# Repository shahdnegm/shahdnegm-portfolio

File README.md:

# Shahd Negm | Manufacturing Systems & Engineering Portfolio

**Mechatronics Engineering graduate · MSc Engineering Management student**  
**Focus:** Manufacturing Execution Systems (MES) · Manufacturing Operations Management (MOM) · Smart Manufacturing · Quality & Production Data

I bring hands-on manufacturing experience using **MES at Schaeffler**, alongside academic work in automated inspection, reliability simulation and manufacturing process improvement.

## Shop-floor MES experience

At **Schaeffler**, I used the manufacturing execution system to:
- Track production items and inspect their manufacturing history and **traceability**.
- Check and record quality-related information and **quality decisions**, including whether an item was marked for **scrap or rework**.
- Verify the **next step** in an item's production workflow.
- Record completed process steps so the item's manufacturing progress could be followed.

This describes **operational use of an existing MES**, not software development or system administration. My experience supports my interest in improving the digital connection between quality decisions and shop-floor execution.

## Featured manufacturing projects

| Project | Problem / technical contribution | Evidence |
|---|---|---|
| [AI-Powered Automated Optical Inspection](projects/automated-optical-inspection/README.md) | Built a vision-based inspection prototype integrating quality decisions and traceability logging | [Peer-reviewed first-author publication](https://doi.org/10.1007/s00170-026-18704-3); 33-bottle benchmark |
| [Monte Carlo Production-Line Reliability](projects/monte-carlo-reliability.md) | Analysed buffer sizing, failures, preventive maintenance, throughput and bottlenecks | Team evaluated 125 configurations, 1,000 replications each |
| [Unilever Industrial Engineering Competition](projects/unilever-industrial-engineering.md) | Designed manufacturing-flow and changeover improvement concepts | Quantified *proposed* time reductions and estimated business impact |
| [Olist E-Commerce Delivery Reliability — Six Sigma DMAIC](projects/olist-delivery-dmaic/README.md) | Historical order-level delivery KPI analysis, freight/geography segmentation, Ishikawa and proposed pilot/control plans | 96,470 eligible deliveries; 6.77% provisional date-based late rate |
| [Fapofa Quality & Process Improvement](projects/fapofa-process-improvement.md) | Mapped processes and proposed quality-control and Lean improvements | Team academic case study using Pareto, Fishbone and PDCA |

## Other technical projects

- [Robotic Manipulator Arm](projects/robotic-manipulator-arm/README.md) — design and control reports, 11 mechanical drawings, KiCad electronics, MATLAB code and Simulink model.
- [Line-Following Robot](projects/line-follower-robot.md) — sensors, Arduino and drive control.

## Technical toolkit

**Manufacturing & quality:** MES workflow use, item traceability, scrap/rework decisions, AOI/X-ray inspection, process mapping, SMED, PDCA.  
**Analysis & simulation:** Python, Excel, Monte Carlo simulation, reliability analysis, production KPIs, MATLAB/Simulink.  
**Automation & inspection:** YOLOv8, image processing, OCR, PLC interface concepts and CAD.

## Publication

Negm, Shahd Ayman, et al. (2026). *Vision-based automated optical inspection for real-time quality control: hybrid single-camera deep-learning AOI for mixed-SKU bottling lines.* *The International Journal of Advanced Manufacturing Technology*. [Read publication](https://doi.org/10.1007/s00170-026-18704-3).

## Attribution and sharing policy

Monte Carlo and Fapofa were **academic team projects**. Pages distinguish individual and team contributions. Simulated results, proposed targets and estimated savings are **not implemented industrial outcomes**. The Monte Carlo workbook and Python simulation are public; the AOI project's scripts and datasets are not publicly released.

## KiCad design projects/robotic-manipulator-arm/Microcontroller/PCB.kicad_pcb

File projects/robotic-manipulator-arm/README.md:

# Four-DOF Robotic Manipulator Arm

Academic mechatronics project · University of Debrecen · 2025

A four-degree-of-freedom robotic-arm design for light industrial drilling, combining mechanical design, motor and encoder selection, a KiCad controller design, and MATLAB/Simulink motor-control modelling.

## Project figures

*Final CAD assembly — design report Fig. 2, PDF p. 4.*

*KiCad motor-controller PCB — design report Fig. 3, PDF p. 6.*

*Simulated controller-response comparison — design report Fig. 6, PDF p. 8.*

[Browse all seven original figures](GALLERY.md), including the base CAD, wiring diagram, cascade-current response and Simulink control structure.

## Project files

| Area | Files |
|---|---|
| Design report | [Project description](Project-description.pdf) |
| Motor-control report | [PI, PID and cascade-control analysis](PID/PID-analysis.pdf) |
| MATLAB | [Motor model and controller calculations](PID/code.m) |
| Simulink | [Motor-control model](PID/simulink.slx) |
| Electronics | [PCB layout](Microcontroller/PCB.kicad_pcb), [schematic](Microcontroller/schematic.kicad_sch), [KiCad project settings](Microcontroller/Project.kicad_pro) |
| Mechanical assembly | [Assembly drawing](drawings/Assembly.pdf), [exploded view](drawings/Exploded-view.pdf) |
| Components | [Base](drawings/Base.pdf), [upper base](drawings/upper-base.pdf), [main arm](drawings/main-arm.pdf), [motor](drawings/Motor.pdf), [motor casing](drawings/Motor-casing.pdf), [motor top](drawings/motor-top.pdf), [shaft](drawings/shaft.pdf), [shaft aligner](drawings/shaft-aligner.pdf), [end effector](drawings/end-effector.pdf) |

All 18 source files from the robotic-arm archive are represented here. Public PDFs and the MATLAB header have the university student ID removed. Technical content is otherwise retained.

## Engineering scope

- Mechanical assembly and dimensioned component drawings.
- Maxon DCX 22 S motor and ENX 10 EASY encoder selection.
- ATmega328P-based controller design with VNH5019A-E motor driver.
- DC motor transfer-function modelling and comparison of PI, PID and cascade current/speed control.
- Simulation-based study of tracking, current response and voltage saturation.

This is an academic design and simulation portfolio. The reports describe the work performed; the files do not independently establish physical hardware performance or production readiness.

## Open and use the files

**Reports and drawings:** open the PDFs in a PDF viewer. Use GitHub's download control for a local copy.

**MATLAB and Simulink:** download or clone the repository, then use the project PID folder as the MATLAB current folder:

```matlab
cd('projects/robotic-manipulator-arm/PID')
run('code.m')
open_system('simulink.slx')
```

The script uses Symbolic Math Toolbox (`syms`) and Control System Toolbox (`tf`). The model was last saved in MATLAB/Simulink R2024b. Open it in a compatible release and install any additional products reported by its blocks. Review workspace parameters and block settings before running a simulation. MATLAB execution has not been independently rerun for this publication.

**KiCad:** open the PCB and schematic directly in a compatible KiCad release. The archived settings file is named `Project.kicad_pro`, while the PCB and schematic have different base names. Preserve the provided files when inspecting them; linking them into a single renamed KiCad project is a separate editing step.

The mechanical deliverables supplied in the archive are PDF drawings; no native mechanical CAD assembly or microcontroller firmware was present in this folder.

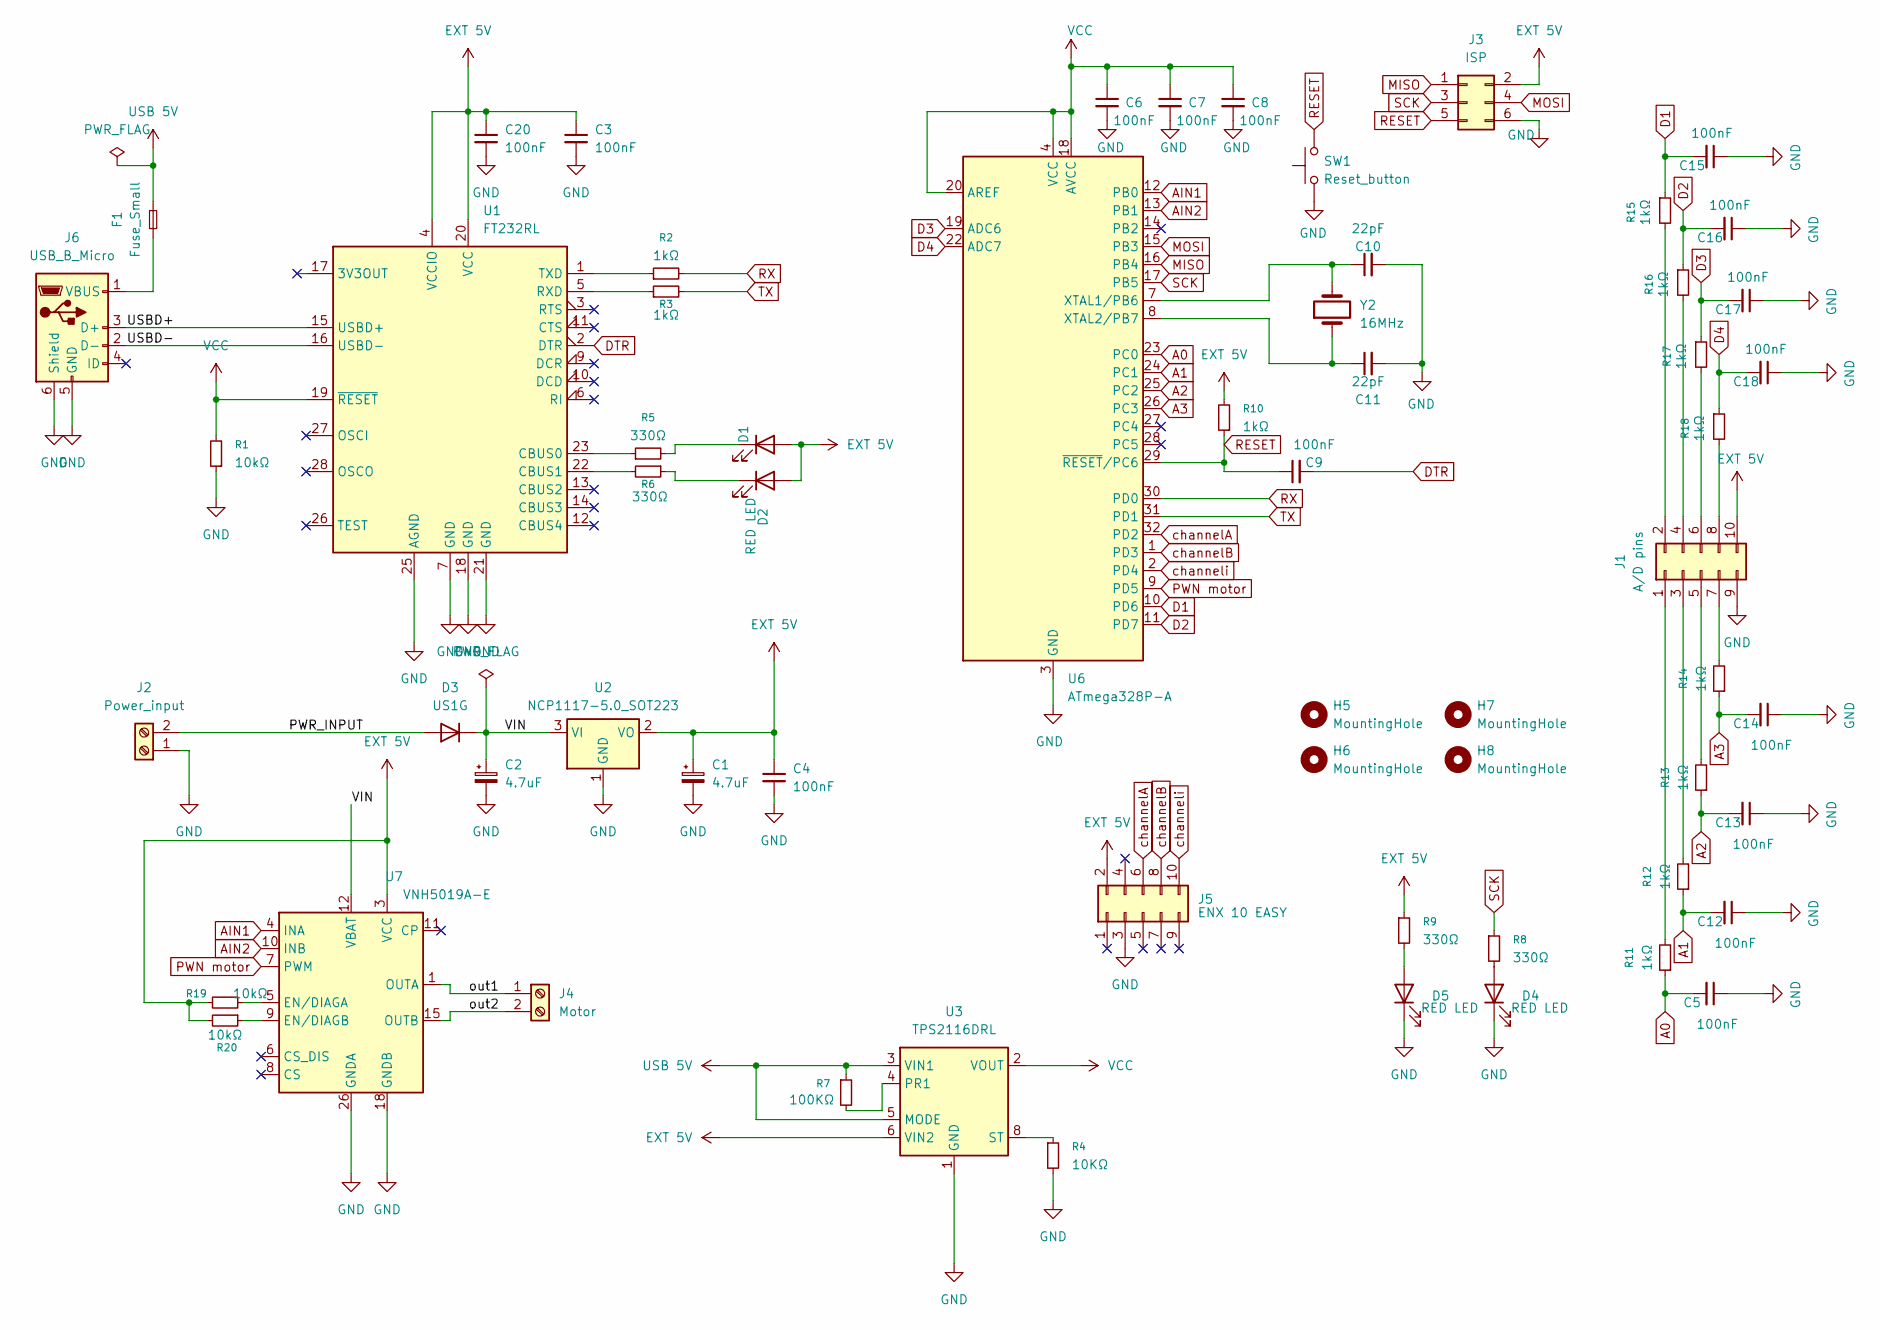
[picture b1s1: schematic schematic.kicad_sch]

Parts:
C1, C2: 4.7uF; CP_EIA-3216-18_Kemet-A
C3, C20: 100nF; C_0805_2012Metric_Pad1.18x1.45mm_HandSolder
C4, C5, C6, C7, C8, C9, C12, C13, C14, C15, C16, C17, C18: 100nF; C_0805_2012Metric
C10, C11: 22pF; C_0805_2012Metric
D1, D2, D4, D5: RED LED; LED_1206_3216Metric
D3: US1G; D_SMA
F1: Fuse_Small; Fuse_0805_2012Metric_Pad1.15x1.40mm_HandSolder
H5, H6, H7, H8: MountingHole; MountingHole_3.2mm_M3
J1: A/D pins; PinHeader_2x05_P1.27mm_Vertical
J2: Power_input; TerminalBlock_Phoenix_MPT-0,5-2-2.54_1x02_P2.54mm_Horizontal
J3: ISP; PinHeader_2x03_P2.54mm_Vertical
J4: Motor; TerminalBlock_Phoenix_MPT-0,5-2-2.54_1x02_P2.54mm_Horizontal
J5: ENX 10 EASY; PinHeader_2x05_P1.27mm_Vertical
J6: USB_B_Micro; USB_Micro-B_Molex_47346-0001
R1, R19, R20: 10kΩ; R_0805_2012Metric
R2, R3, R10, R11, R12, R13, R14, R15, R16, R17, R18: 1kΩ; R_0805_2012Metric
R4: 10KΩ; R_0805_2012Metric
R5, R6, R8, R9: 330Ω; R_0805_2012Metric
R7: 100KΩ; R_0805_2012Metric
SW1: Reset_button; SW_SPST_B3U-1000P
U1: FT232RL; SSOP-28_5.3x10.2mm_P0.65mm
U2: NCP1117-5.0_SOT223; SOT-223-3_TabPin2
U3: TPS2116DRL; SOT-583-8
U6: ATmega328P-A; TQFP-32_7x7mm_P0.8mm
U7: VNH5019A-E; ST_MultiPowerSO-30
Y2: 16MHz; Crystal_SMD_HC49-SD

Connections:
/PWR_INPUT: D3.2 (A), J2.2
/USBD+: J6.3 (D+), U1.15 (USBD+)
/USBD-: J6.2 (D-), U1.16 (USBD-)
/VIN: C2.1, D3.1 (K), U2.3 (VI), U7.12 (VBAT)
/out1: J4.1, U7.1 (OUTA), U7.25 (OUTA), U7.30 (OUTA), U7.33 (OUTA)
/out2: J4.2, U7.15 (OUTB), U7.16 (OUTB), U7.21 (OUTB), U7.32 (OUTB)
A0: C5.2, R11.1, U6.23 (PC0)
A1: C12.2, R12.1, U6.24 (PC1)
A2: C13.2, R13.1, U6.25 (PC2)
A3: C14.2, R14.1, U6.26 (PC3)
AIN1: U6.12 (PB0), U7.4 (INA)
AIN2: U6.13 (PB1), U7.10 (INB)
D1: C15.2, R15.1, U6.10 (PD6)
D2: C16.2, R16.1, U6.11 (PD7)
D3: C17.2, R17.1, U6.19 (ADC6)
D4: C18.2, R18.1, U6.22 (ADC7)
DTR: C9.2, U1.2 (DTR)
EXT 5V: C1.1, C3.1, C4.1, C20.1, D1.2 (A), D2.2 (A), J1.10, J3.2, J5.2, R9.1, R10.2, R19.2, R20.2, U1.4 (VCCIO), U1.20 (VCC), U2.2 (VO), U3.6 (VIN2), U7.3 (VCC), U7.13 (VCC), U7.23 (VCC), U7.31 (VCC)
GND: C1.2, C2.2, C3.2, C4.2, C5.1, C6.2, C7.2, C8.2, C10.2, C11.2, C12.1, C13.1, C14.1, C15.1, C16.1, C17.1, C18.1, C20.2, D4.1 (K), D5.1 (K), J1.9, J2.1, J3.6, J5.3, J6.5 (GND), J6.6 (Shield), R1.1, R4.2, SW1.1, U1.7 (GND), U1.18 (GND), U1.21 (GND), U1.25 (AGND), U2.1 (GND), U3.1 (GND), U6.3 (GND), U6.5 (GND), U6.21 (GND), U7.18 (GNDB), U7.19 (GNDB), U7.20 (GNDB), U7.26 (GNDA), U7.27 (GNDA), U7.28 (GNDA)
MISO: J3.1, U6.16 (PB4)
MOSI: J3.4, U6.15 (PB3)
unnamed: D1.1 (K), R5.2
unnamed: D2.1 (K), R6.1
unnamed: D4.2 (A), R8.2
unnamed: D5.2 (A), R9.2
unnamed: J1.1, R11.2
unnamed: J1.2, R15.2
unnamed: J1.3, R12.2
unnamed: J1.4, R16.2
unnamed: J1.5, R13.2
unnamed: J1.6, R17.2
unnamed: J1.7, R14.2
unnamed: J1.8, R18.2
unnamed: F1.1, J6.1 (VBUS)
unnamed: R5.1, U1.23 (CBUS0)
unnamed: R6.2, U1.22 (CBUS1)
unnamed: R3.1, U1.5 (RXD)
unnamed: R2.1, U1.1 (TXD)
unnamed: R7.2, U3.4 (PR1)
unnamed: R4.1, U3.8 (ST)
unnamed: C10.1, U6.7 (XTAL1/PB6), Y2.2
unnamed: C11.1, U6.8 (XTAL2/PB7), Y2.1
unnamed: R19.1, U7.5 (EN/DIAGA)
unnamed: R20.1, U7.9 (EN/DIAGB)
PWN motor: U6.9 (PD5), U7.7 (PWM)
RESET: C9.1, J3.5, R10.1, SW1.2, U6.29 (~RESET/PC6)
RX: R2.2, U6.30 (PD0)
SCK: J3.3, R8.1, U6.17 (PB5)
TX: R3.2, U6.31 (PD1)
USB 5V: F1.2, R7.1, U3.3 (VIN1), U3.5 (MODE)
VCC: C6.1, C7.1, C8.1, R1.2, U1.19 (~RESET), U3.2 (VOUT), U3.7 (VOUT), U6.4 (VCC), U6.6 (VCC), U6.18 (AVCC), U6.20 (AREF)
channelA: J5.6, U6.32 (PD2)
channelB: J5.8, U6.1 (PD3)
channeli: J5.10, U6.2 (PD4)

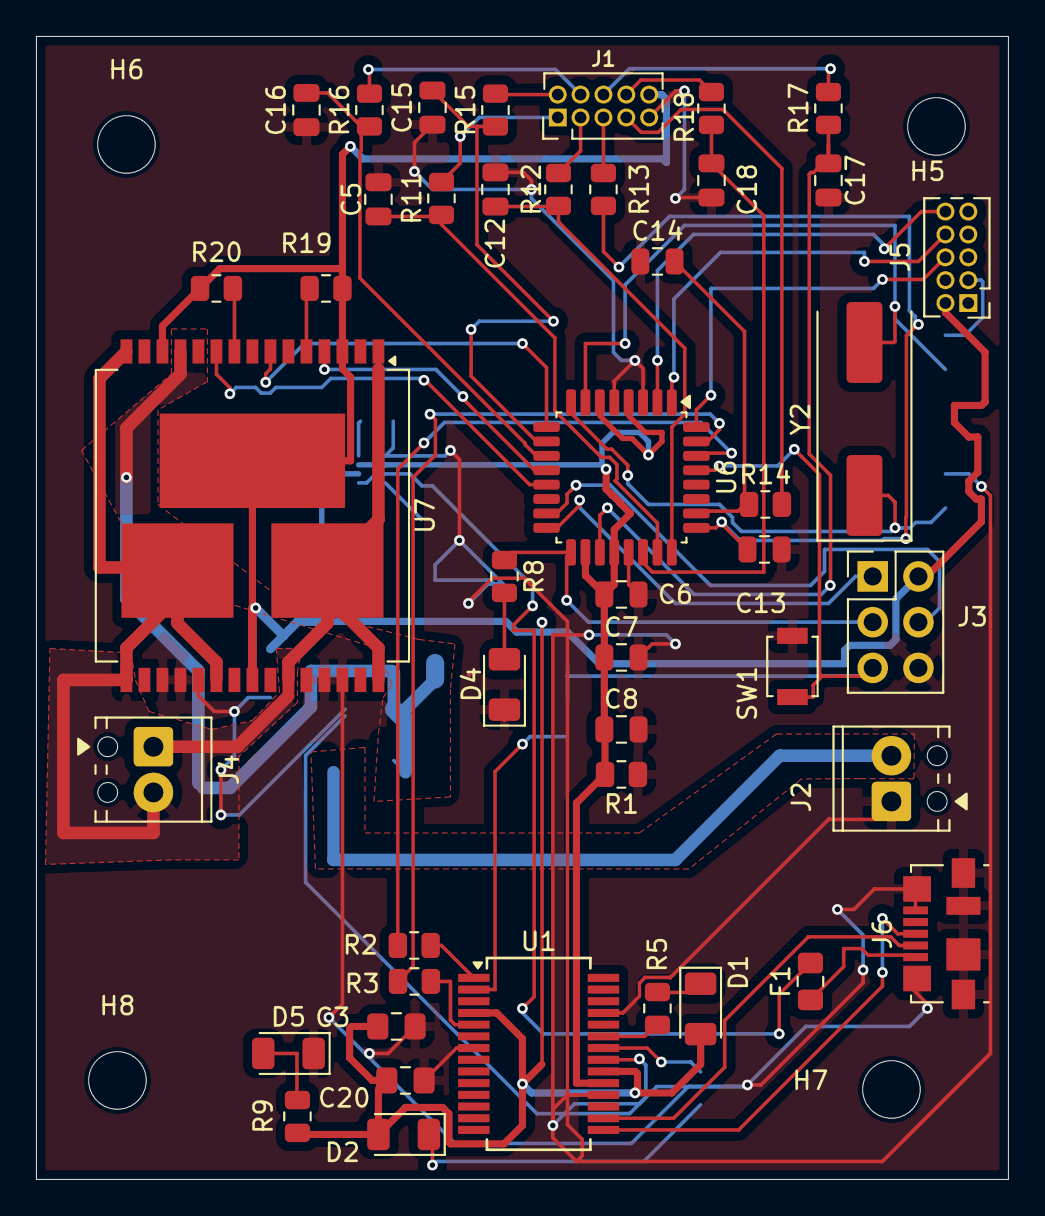
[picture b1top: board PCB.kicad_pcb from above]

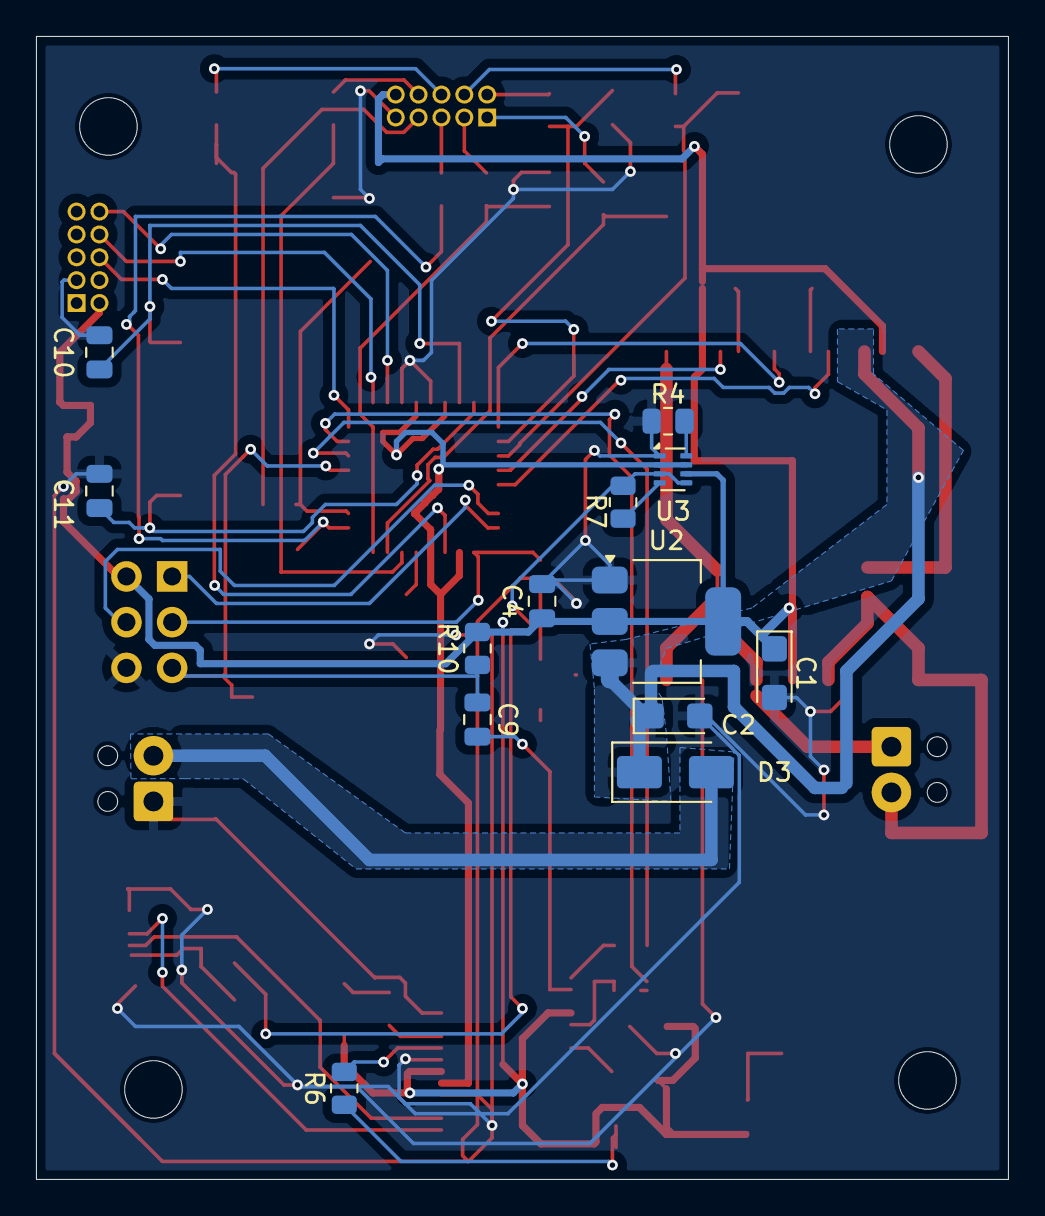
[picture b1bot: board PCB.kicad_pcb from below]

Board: 2 copper layers, 54.0 x 63.5 mm, 62 parts (13 on the bottom side), 54 nets.
